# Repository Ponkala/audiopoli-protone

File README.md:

# audiopoli-protone
Repo for sharing matlab scripts and other files for the DIY active speakers. 
<br><br>
IRtoFR.m reads the data from a measured sweep and outputs a .frd file.<br>
IRtoFR_sum.m read the data from a measured IR data and outputs a .frd file for all different measurement angles.

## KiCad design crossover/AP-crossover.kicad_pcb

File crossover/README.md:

# Docs for active crossover
## Front view

## Back view

## Schematic

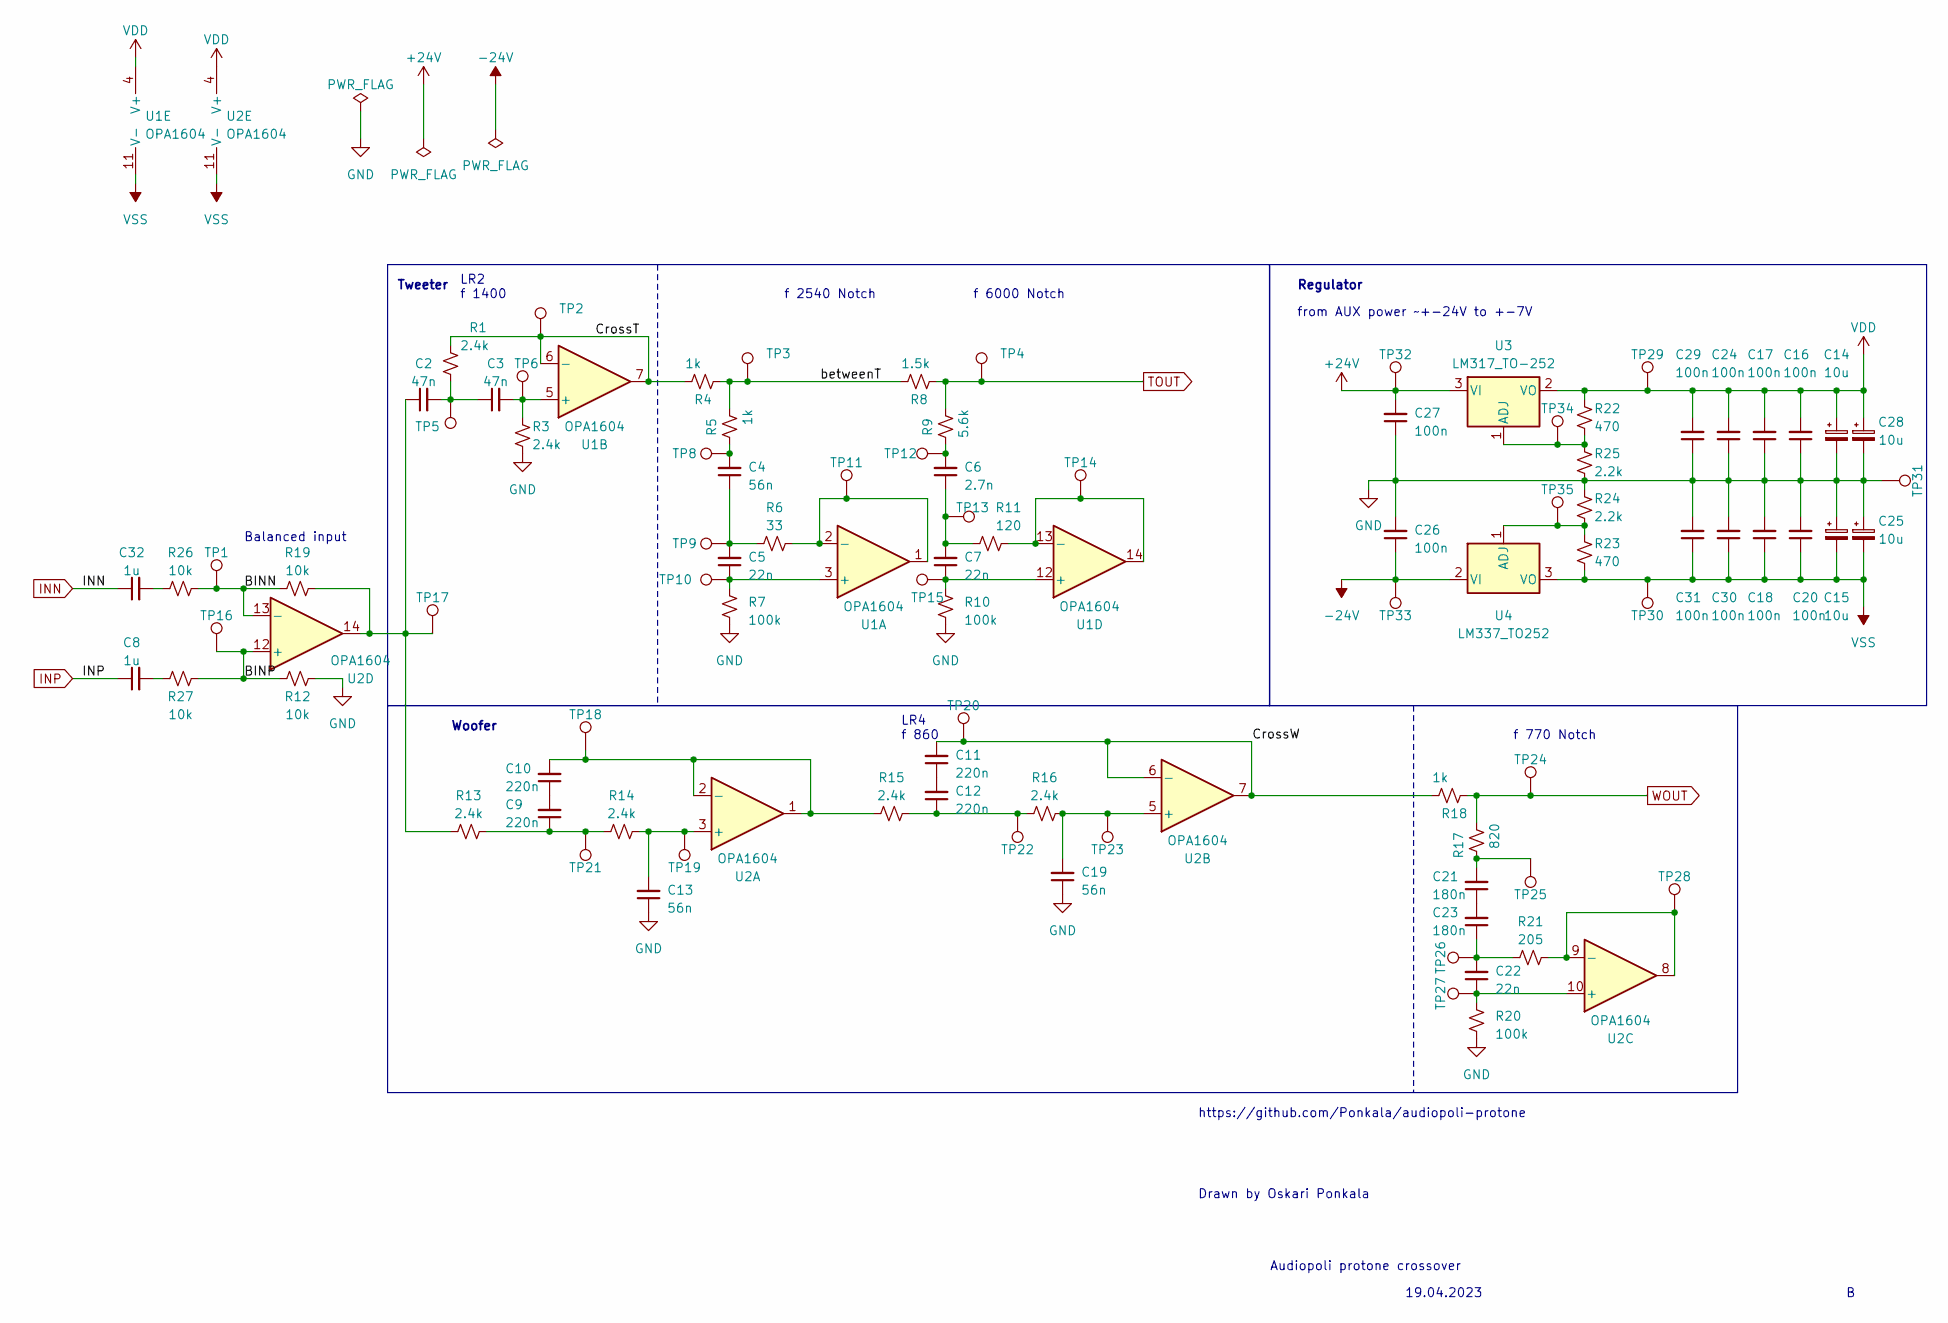
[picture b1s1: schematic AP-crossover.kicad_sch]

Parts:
C2, C3: 47n; C_0603_1608Metric
C4, C13, C19: 56n; C_0603_1608Metric
C5, C7, C22: 22n; C_0603_1608Metric
C6: 2.7n; C_0603_1608Metric
C8, C32: 1u; C_0805_2012Metric
C9, C10, C11, C12: 220n; C_0603_1608Metric
C14, C15, C25, C28: 10u; CP_Elec_5x5.4
C16, C17, C18, C20, C24, C26, C27, C29, C30, C31: 100n; C_0805_2012Metric
C21, C23: 180n; C_0603_1608Metric
R1, R3, R13, R14, R15, R16: 2.4k; R_0603_1608Metric
R4, R5, R18: 1k; R_0603_1608Metric
R6: 33; R_0603_1608Metric
R7, R10, R20: 100k; R_0603_1608Metric
R8: 1.5k; R_0603_1608Metric
R9: 5.6k; R_0603_1608Metric
R11: 120; R_0603_1608Metric
R12, R19, R26, R27: 10k; R_0603_1608Metric
R17: 820; R_0603_1608Metric
R21: 205; R_0603_1608Metric
R22, R23: 470; R_0805_2012Metric
R24, R25: 2.2k; R_0805_2012Metric
TP1, TP2, TP3, TP4, TP5, TP6, TP8, TP9, TP10, TP11, TP12, TP13, TP14, TP15, TP16, TP17, TP18, TP19, TP20, TP21, TP22, TP23, TP24, TP25, TP26, TP27, TP28, TP29, TP30, TP31, TP32, TP33, TP34, TP35: TestPoint; TestPoint_THTPad_D1.0mm_Drill0.5mm
U1, U2: OPA1604; TSSOP-14_4.4x5mm_P0.65mm
U3: LM317_TO-252; TO-252-2
U4: LM337_TO252; TO-252-2

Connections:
+24V: C27.2, TP32.1, U3.3 (VI); also elsewhere on the board
-24V: C26.1, TP33.1, U4.2 (VI); also elsewhere on the board
/BINN: R19.1, R26.1, TP1.1, U2.13 (-)
/BINP: R12.1, R27.2, TP16.1, U2.12 (+)
/CrossT: R1.1, R4.2, TP2.1, U1.6 (-), U1.7
/CrossW: C11.2, R18.2, TP20.1, U2.6 (-), U2.7
/betweenT: R4.1, R5.2, R8.2, TP3.1
GND: C13.1, C14.2, C15.1, C16.1, C17.1, C18.2, C19.1, C20.2, C24.1, C25.1, C26.2, C27.1, C28.2, C29.1, C30.2, C31.2, R3.2, R7.1, R10.1, R12.2, R20.1, R24.1, R25.2, TP31.1; also elsewhere on the board
INN: C32.1; also elsewhere on the board
INP: C8.1; also elsewhere on the board
unnamed: C2.1, R13.2, R19.2, TP17.1, U2.14
unnamed: C2.2, C3.1, R1.2, TP5.1
unnamed: C4.1, C5.2, R6.1, TP9.1
unnamed: C4.2, R5.1, TP8.1
unnamed: C6.1, C7.2, R11.1, TP13.1
unnamed: C6.2, R9.1, TP12.1
unnamed: C8.2, R27.1
unnamed: C9.1, R13.1, R14.2, TP21.1
unnamed: C9.2, C10.1
unnamed: C11.1, C12.2
unnamed: C12.1, R15.1, R16.2, TP22.1
unnamed: C21.1, C23.2
unnamed: C21.2, R17.1, TP25.1
unnamed: C22.2, C23.1, R21.1, TP26.1
unnamed: C32.2, R26.2
unnamed: C5.1, R7.2, TP10.1, U1.3 (+)
unnamed: R6.2, TP11.1, U1.1, U1.2 (-)
unnamed: C3.2, R3.1, TP6.1, U1.5 (+)
unnamed: C7.1, R10.2, TP15.1, U1.12 (+)
unnamed: R11.2, TP14.1, U1.13 (-), U1.14
unnamed: C13.2, R14.1, TP19.1, U2.3 (+)
unnamed: C10.2, R15.2, TP18.1, U2.1, U2.2 (-)
unnamed: C19.2, R16.1, TP23.1, U2.5 (+)
unnamed: C22.1, R20.2, TP27.1, U2.10 (+)
unnamed: R21.2, TP28.1, U2.8, U2.9 (-)
unnamed: R22.2, R25.1, TP34.1, U3.1 (ADJ)
unnamed: R23.1, R24.2, TP35.1, U4.1 (ADJ)
TOUT: R8.1, R9.2, TP4.1; also elsewhere on the board
VDD: C14.1, C16.2, C17.2, C24.2, C28.1, C29.2, R22.1, TP29.1, U1.4 (V+), U2.4 (V+), U3.2 (VO)
VSS: C15.2, C18.1, C20.1, C25.2, C30.1, C31.1, R23.2, TP30.1, U1.11 (V-), U2.11 (V-), U4.3 (VO)
WOUT: R17.2, R18.1, TP24.1; also elsewhere on the board

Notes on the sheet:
from AUX power ~+-24V to +-7V
f 6000 Notch
f 770 Notch
Drawn by Oskari Ponkala
LR4 f 860
Audiopoli protone crossover
https://github.com/Ponkala/audiopoli-protone
Regulator
19.04.2023
LR2 f 1400
Woofer
f 2540 Notch
Balanced input
Tweeter

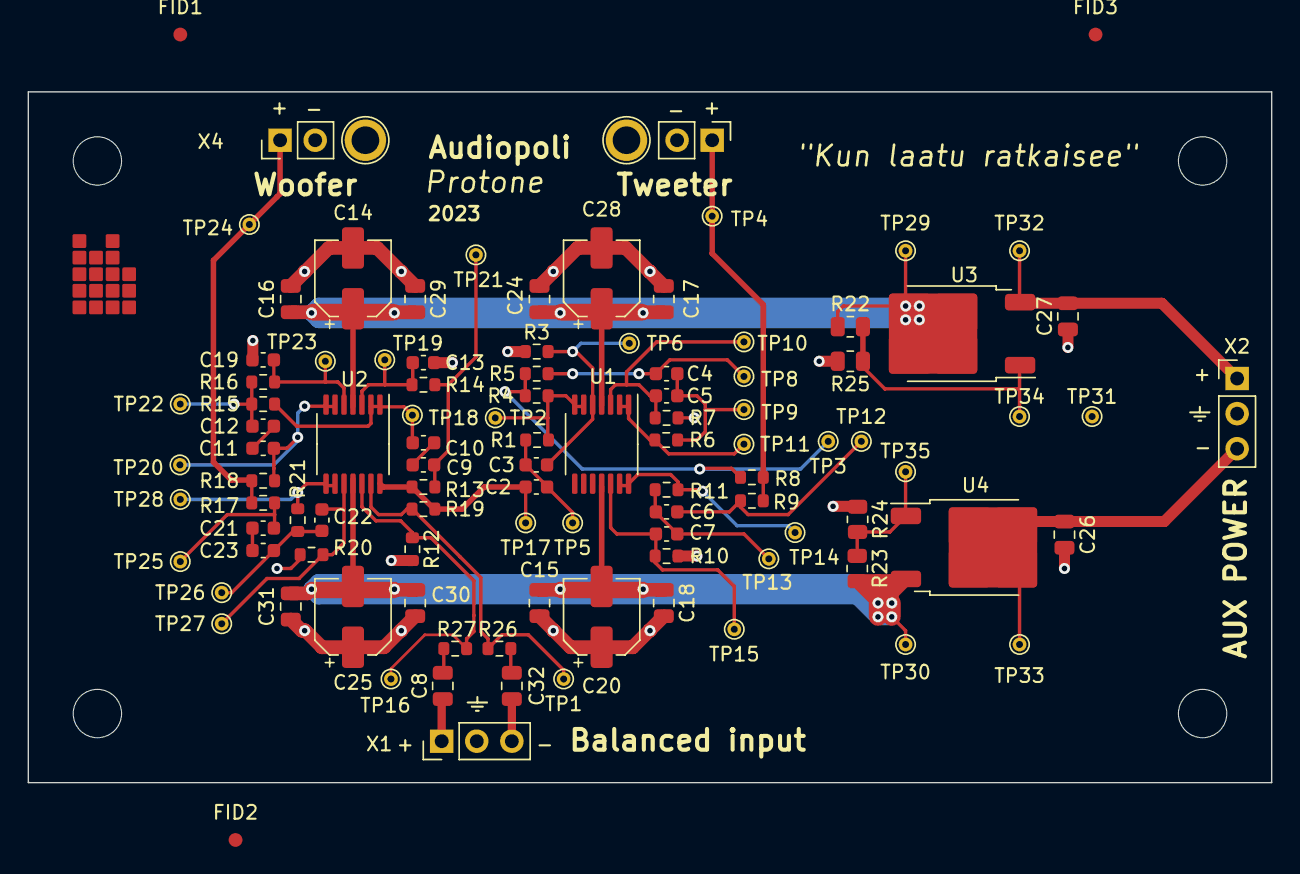
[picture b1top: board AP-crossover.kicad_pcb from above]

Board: 4 copper layers, 90.0 x 50.0 mm, 106 parts (0 on the bottom side), 41 nets.

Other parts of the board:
FID1, FID2, FID3: Fiducial_1mm_Mask2mm
H1, H2, H3, H4: MountingHole_3.5mm
X1, X2: PinHeader_1x03_P2.54mm_Vertical
X3, X4: PinHeader_1x02_P2.54mm_Vertical

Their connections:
+24V: X2.1; also elsewhere on the board
-24V: X2.3; also elsewhere on the board
GND: X1.2, X2.2, X3.2, X4.2; also elsewhere on the board
INN: X1.3; also elsewhere on the board
INP: X1.1; also elsewhere on the board
TOUT: X3.1; also elsewhere on the board
WOUT: X4.1; also elsewhere on the board

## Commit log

2023-04-12 Initial commit
    add few scripts for calculating FRD from IR data
2023-04-12 Create README.md
    add some text
2023-04-13 make colorcheme nicer, add titles to plots
2023-04-13 add better plots
2023-04-14 add nicer plotting, such as colorbar
2023-04-17 Add kicad files
    first pcb layout revision
2023-05-03 Update pcb layout to revision B, add balanced input
2023-05-06 Add git hub action to create board preview.
    Also clean up Tiltle block so that the svg export works correct
2023-05-06 Show GitHub Actions logo
2023-05-06 Change the readme label
    crossover for active crossover -> Docs for active crossover
2023-05-06 Add regulator voltage levels
2023-05-06 Update AP-crossover.kicad_pcb
    Change visibility of comment layer so that the svg export does not include this in page size calc
2023-05-06 Update AP-crossover.kicad_pcb
    Change visabiliy of comment layer to fix scaling of svg export
2023-05-06 Update docs.yml
    Update message
2023-05-06 Github actions at work
2023-05-06 Forgot to fill areas before commit
